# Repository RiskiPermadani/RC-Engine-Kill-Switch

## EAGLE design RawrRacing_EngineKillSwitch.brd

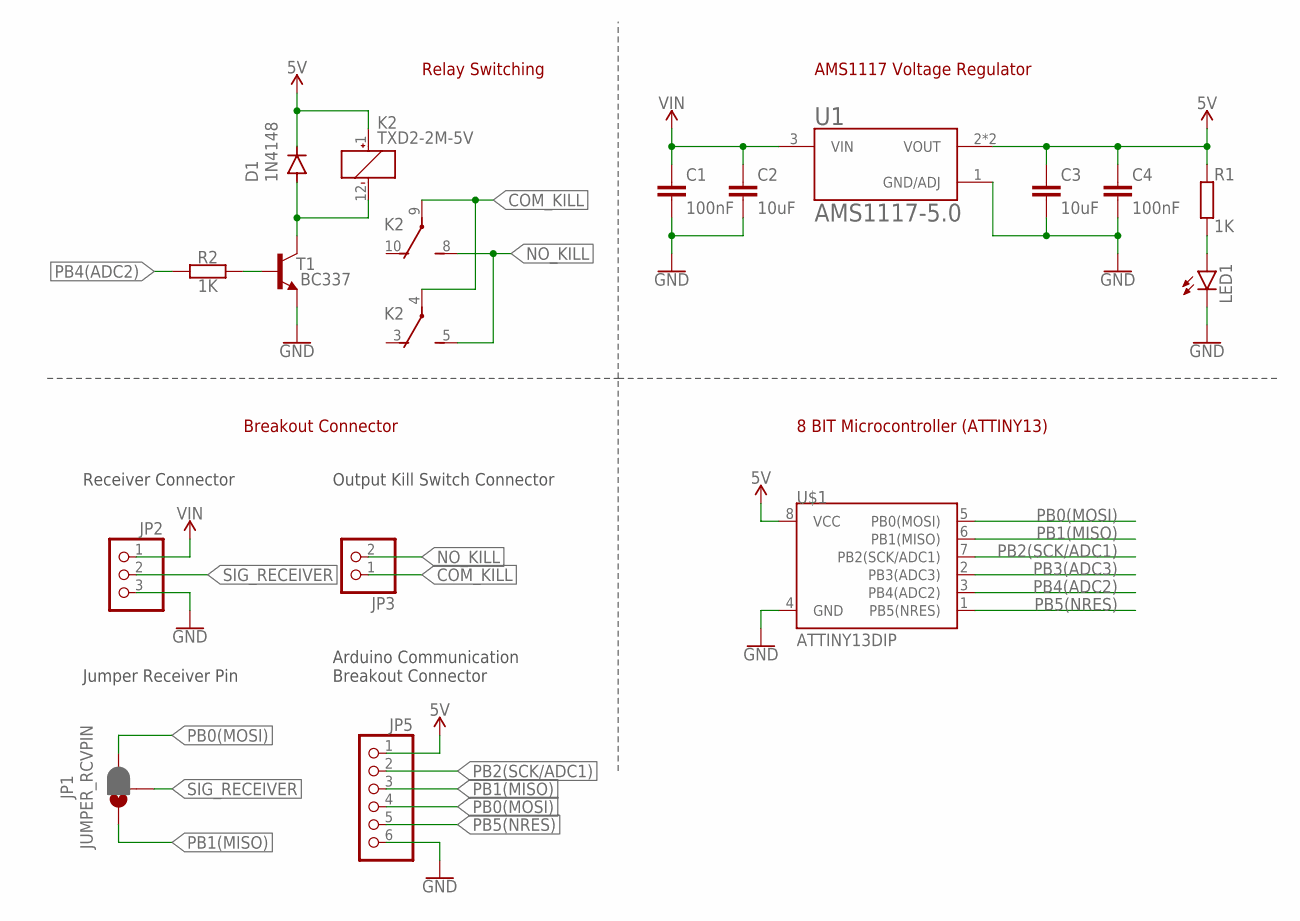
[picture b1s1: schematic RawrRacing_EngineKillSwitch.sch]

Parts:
C1, C4: 100nF; C0603
C2, C3: 10uF; C0603
D1: 1N4148; SOD80C
JP1: JUMPER_RCVPIN; SMT-JUMPER_3_1-NC_PASTE_SILK
JP2: PINHD-1X3/90; 1X03/90
JP3: PINHD-1X2/90; 1X02/90
JP5: PINHD-1X6; 1X06
K2: TXD2-2M-5V; TXD2
LED1: LEDSML0603; SML0603
R1, R2: 1K; R0603
T1: BC337; TO92
U1: AMS1117-5.0; SOT229P700X180-4N
U$1: ATTINY13DIP; DIP08_MCU

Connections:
5V: C3.1, C4.1, D1.C, JP5.1, K2.1 (+), R1.1, U1.2 (VOUT), U1.4 (VOUT), U$1.8 (VCC)
COM_KILL: JP3.1, K2.4, K2.9
GND: C1.2, C2.2, C3.2, C4.2, JP2.3, JP5.6, LED1.C, T1.1 (E), U1.1 (GND/ADJ), U$1.4 (GND)
unnamed: LED1.A, R1.2
unnamed: D1.A, K2.12 (-), T1.3 (C)
unnamed: R2.2, T1.2 (B)
NO_KILL: JP3.2, K2.5 (S), K2.8 (S)
PB0(MOSI): JP1.3, JP5.4, U$1.5 (PB0(MOSI))
PB1(MISO): JP1.1, JP5.3, U$1.6 (PB1(MISO))
PB2(SCK/ADC1): JP5.2, U$1.7 (PB2(SCK/ADC1))
PB3(ADC3): U$1.2 (PB3(ADC3))
PB4(ADC2): R2.1, U$1.3 (PB4(ADC2))
PB5(NRES): JP5.5, U$1.1 (PB5(NRES))
SIG_RECEIVER: JP1.2, JP2.2
VIN: C1.1, C2.1, JP2.1, U1.3 (VIN)

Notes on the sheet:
AMS1117 Voltage Regulator
Relay Switching
8 BIT Microcontroller (ATTINY13)
Breakout Connector
Arduino Communication Breakout Connector
Output Kill Switch Connector
Receiver Connector
Jumper Receiver Pin

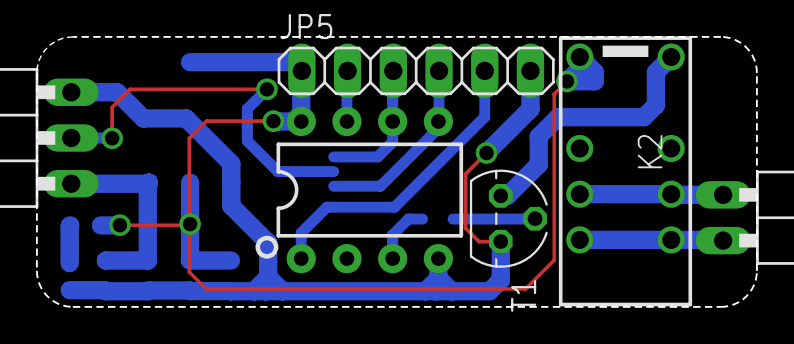
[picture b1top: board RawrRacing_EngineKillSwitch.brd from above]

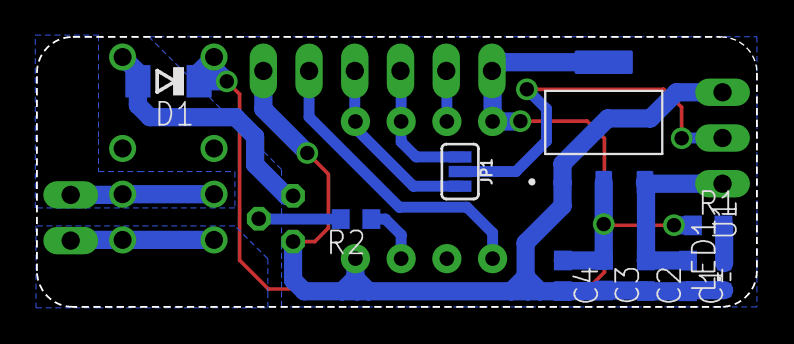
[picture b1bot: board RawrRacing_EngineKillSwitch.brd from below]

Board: 2 copper layers, 40.0 x 15.0 mm, 16 parts (10 on the bottom side), 14 nets.

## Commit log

2023-11-10 Create Hardware

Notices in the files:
parts and their libraries:
SparkFun-Retired: Licensing: Creative Commons ShareAlike 4.0 International - https://creativecommons.org/licenses/by-sa/4.0
